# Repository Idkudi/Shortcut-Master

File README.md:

# Shortcut-Master
A macro pad with oled display

Schematics

Pcb

Pcb in 3d view

pcb in case

Case

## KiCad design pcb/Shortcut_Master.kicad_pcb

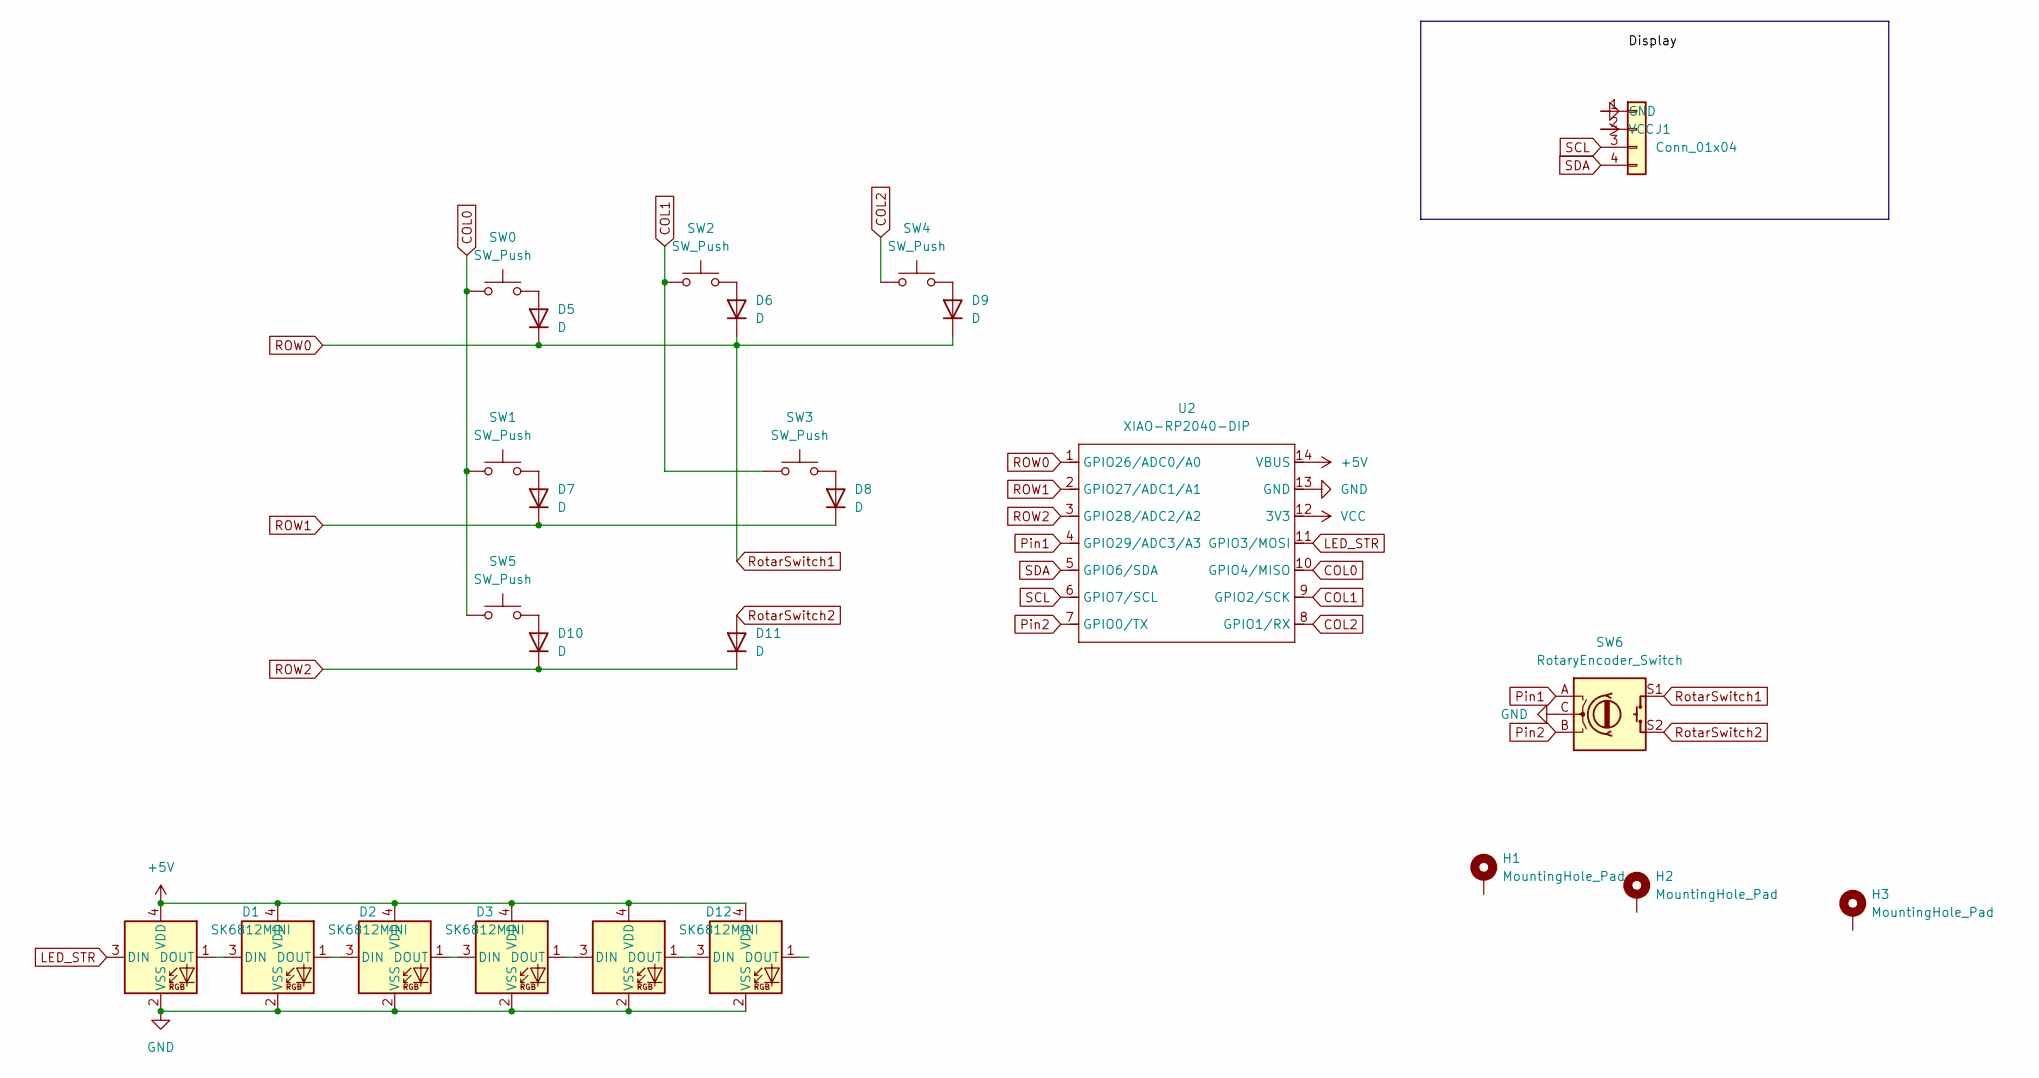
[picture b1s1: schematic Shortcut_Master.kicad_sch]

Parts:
D1, D2, D3, D4, D12, D13: SK6812MINI; MX_SK6812MINI-E_REV
D5, D6, D7, D8, D9, D10, D11: D; D_DO-35_SOD27_P7.62mm_Horizontal
H1, H2, H3: MountingHole_Pad; MountingHole_3.2mm_M3_DIN965_Pad_TopBottom
J1: Conn_01x04; SSD1306-0.91-OLED-4pin-128x32
SW0, SW1, SW2, SW3, SW4, SW5: SW_Push; MX-Solderable-1U
SW6: RotaryEncoder_Switch; RotaryEncoder_Alps_EC11E-Switch_Vertical_H20mm
U2: XIAO-RP2040-DIP

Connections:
+5V: D1.4 (VDD), D2.4 (VDD), D3.4 (VDD), D4.4 (VDD), D12.4 (VDD), D13.4 (VDD), U2.14 (VBUS)
COL0: SW0.1, SW1.1, SW5.1, U2.10 (GPIO4/MISO)
COL1: SW2.1, SW3.1, U2.9 (GPIO2/SCK)
COL2: SW4.1, U2.8 (GPIO1/RX)
GND: D1.2 (VSS), D2.2 (VSS), D3.2 (VSS), D4.2 (VSS), D12.2 (VSS), D13.2 (VSS), J1.1, SW6.C, U2.13 (GND)
LED_STR: D1.3 (DIN), U2.11 (GPIO3/MOSI)
unnamed: D1.1 (DOUT), D2.3 (DIN)
unnamed: D2.1 (DOUT), D3.3 (DIN)
unnamed: D3.1 (DOUT), D4.3 (DIN)
unnamed: D5.2 (A), SW0.2
unnamed: D6.2 (A), SW2.2
unnamed: D7.2 (A), SW1.2
unnamed: D8.2 (A), SW3.2
unnamed: D9.2 (A), SW4.2
unnamed: D10.2 (A), SW5.2
unnamed: D4.1 (DOUT), D12.3 (DIN)
unnamed: D12.1 (DOUT), D13.3 (DIN)
Pin1: SW6.A, U2.4 (GPIO29/ADC3/A3)
Pin2: SW6.B, U2.7 (GPIO0/TX)
ROW0: D5.1 (K), D6.1 (K), D9.1 (K), SW6.S1, U2.1 (GPIO26/ADC0/A0)
ROW1: D7.1 (K), D8.1 (K), U2.2 (GPIO27/ADC1/A1)
ROW2: D10.1 (K), D11.1 (K), U2.3 (GPIO28/ADC2/A2)
RotarSwitch2: D11.2 (A), SW6.S2
SCL: J1.3, U2.6 (GPIO7/SCL)
SDA: J1.4, U2.5 (GPIO6/SDA)
VCC: J1.2, U2.12 (3V3)

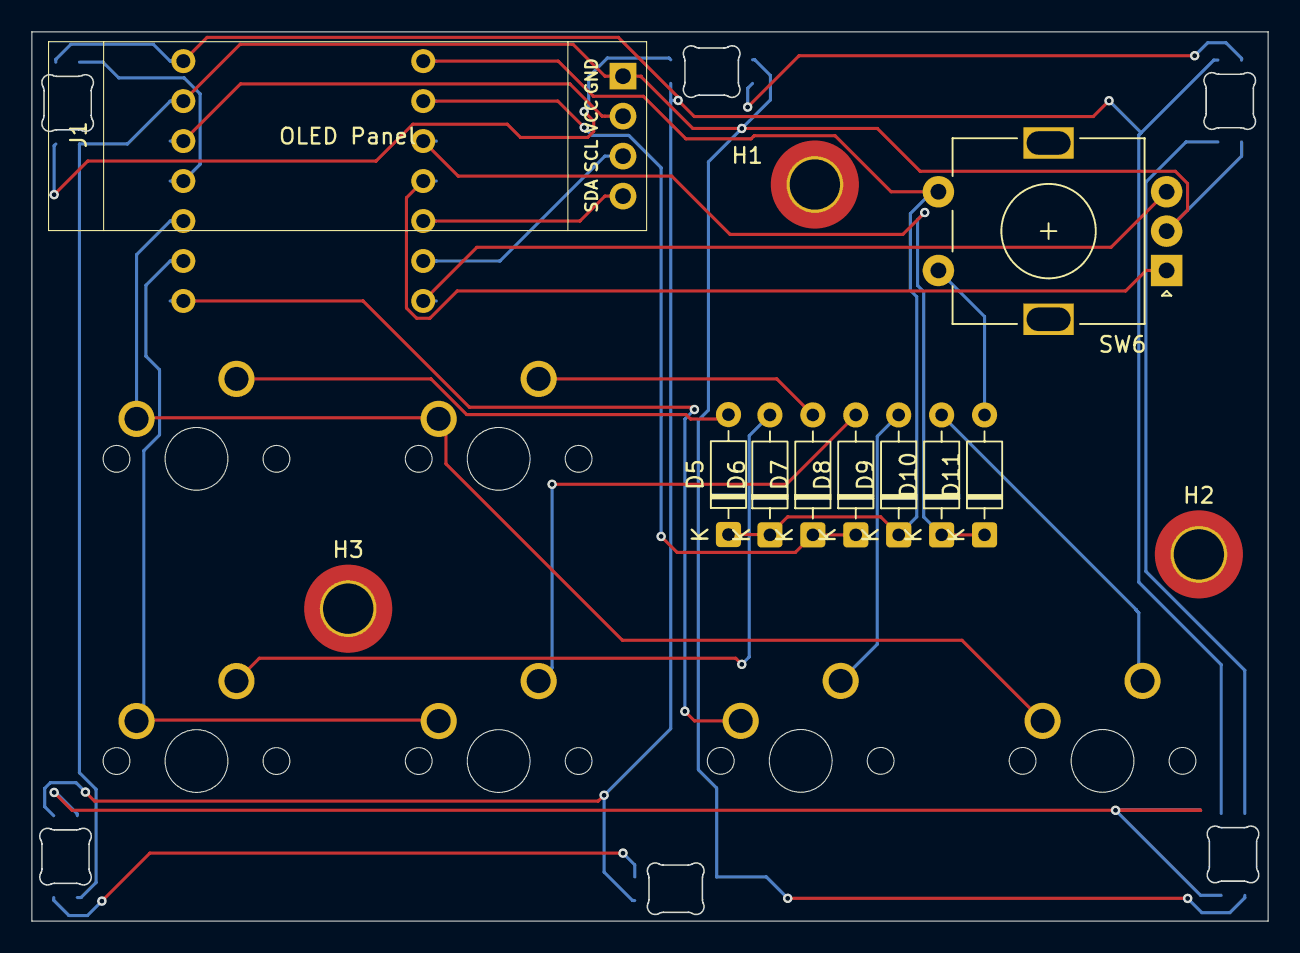
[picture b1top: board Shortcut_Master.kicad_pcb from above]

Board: 2 copper layers, 78.5 x 56.5 mm, 25 parts (1 on the bottom side), 26 nets.

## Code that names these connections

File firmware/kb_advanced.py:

import board
from kmk.kmk_keyboard import KMKKeyboard
from kmk.keys import KC
from kmk.scanners import DiodeOrientation
from kmk.extensions.RGB import RGB
from kmk.modules.encoder import EncoderHandler
from kmk.modules.layers import Layers

# Keyboard Definition
keyboard = KMKKeyboard()

# Add modules
encoder_handler = EncoderHandler()
layers = Layers()
keyboard.modules = [encoder_handler, layers]

# Pin Configuration for XIAO RP2040 based on schematic
# Matrix: 3 rows x 2 columns = 6 keys
# 
# ROW0 = D6 (GPIO28)
# ROW1 = D7 (GPIO29)  
# ROW2 = D10 (GPIO3)
# 
# COL0 and COL1 need to be determined from RotarySwitch connections
# Assuming standard GPIO pins for columns

keyboard.row_pins = (board.D6, board.D7, board.D10)
keyboard.col_pins = (board.D26, board.D27)  # ANPASSEN! Diese Pins basierend auf RotarySwitch verdrahtung

keyboard.diode_orientation = DiodeOrientation.COL2ROW

# RGB LED Configuration
# SK6812MINI LEDs connected in series
# LED_SIG pin needs to be identified from schematic
rgb = RGB(
    pixel_pin=board.D1,  # ANPASSEN! Check welcher Pin für LED_SIG verwendet wird
    num_pixels=6,
    hue_default=100,
    sat_default=100,
    val_default=30,  # Niedrigere Helligkeit um Augen zu schonen
    animation_mode='static_rainbow',
    val_limit=100,
    hue_step=5,
    sat_step=5,
    val_step=5,
    animation_speed=1,
)
keyboard.extensions.append(rgb)

# Rotary Encoder Configuration
# Based on schematic: RotaryEncoder_Switch with Pin1 (GND) and Pin2
encoder_handler.pins = (
    # (pin_a, pin_b, pin_button, is_inverted)
    (board.D8, board.D9, board.D4, False),  # ANPASSEN! Basierend auf tatsächlicher Verdrahtung
)

# Keymap Definition
# Physical layout:
#   SW0  SW2  SW4
#   SW1  SW3  SW5
#
# Matrix layout:
#   [0,0] [0,1]
#   [1,0] [1,1]
#   [2,0] [2,1]

keyboard.keymap = [
    # Layer 0 - Media Controls
    [
        KC.MEDIA_PREV_TRACK,    KC.MEDIA_NEXT_TRACK,    # Row 0
        KC.MEDIA_VOLUME_DOWN,   KC.MEDIA_VOLUME_UP,     # Row 1
        KC.MEDIA_PLAY_PAUSE,    KC.MEDIA_MUTE,          # Row 2
    ],
    
    # Layer 1 - Function Keys (via encoder press)
    [
        KC.F13, KC.F14,  # Row 0
        KC.F15, KC.F16,  # Row 1
        KC.F17, KC.F18,  # Row 2
    ],
    
    # Layer 2 - Numpad
    [
        KC.N7, KC.N8,  # Row 0
        KC.N4, KC.N5,  # Row 1
        KC.N1, KC.N2,  # Row 2
    ],
    
    # Layer 3 - RGB Controls
    [
        KC.RGB_TOG,  KC.RGB_MODE_FORWARD,   # Toggle / Next Mode
        KC.RGB_HUI,  KC.RGB_HUD,            # Hue +/-
        KC.RGB_SAI,  KC.RGB_SAD,            # Saturation +/-
    ],
]

# Encoder Mapping
# Format: ((clockwise, counter_clockwise, button_press),)
encoder_handler.map = [
    # Layer 0 - Volume Control
    ((KC.VOLU, KC.VOLD, KC.MO(1)),),
    
    # Layer 1 - Mouse Scroll
    ((KC.MS_WH_UP, KC.MS_WH_DOWN, KC.TO(2)),),
    
    # Layer 2 - Arrow Keys
    ((KC.UP, KC.DOWN, KC.TO(3)),),
    
    # Layer 3 - RGB Brightness
    ((KC.RGB_VAI, KC.RGB_VAD, KC.TO(0)),),
]

# Debugging
print("XIAO RP2040 Macropad initialized")
print("Layers:", len(keyboard.keymap))
print("Keys per layer:", len(keyboard.keymap[0]))

if __name__ == '__main__':
    keyboard.go()

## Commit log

2026-01-28 without firmware
2026-01-29 new pictures
2026-01-29 Add images and sections to README.md
2026-01-29 Fix spelling of 'Schematics' in README
2026-01-29 Fix schematics image link in README
    Corrected the image link for schematics in README.
2026-01-29 Update project description to specify OLED display
2026-01-30 new picture
2026-01-30 Change PCB image link to relative path
    Updated PCB image link to a relative path.
2026-01-30 .
    .
2026-01-30 Fix image links in README.md
    Updated image links in README and removed local image reference.
2026-01-31 new design
